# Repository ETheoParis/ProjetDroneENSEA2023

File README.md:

# ProjetDroneENSEA2023

I. Introduction :

Nous avons choisi de constituer un groupe de 5 personnes pour asservir et concevoir le PCB d'un drone. La structure en impression 3D nous a été fourni, nous nous sommes donc penchés sur la partie électronique et informatique.
Selon le dictionnaire Larousse, un drone "est un petit avion télécommandé utilisé pour des tâches diverses". Dans notre cas, le cahier des charges impose que notre drone puisse décoller, voler de manière rectiligne et atterrir après avoir volé pendant x mètres. 
Pour satisfaire le cahier des charges, nous avons divisé le travail entre les membres du groupe. Jack Du, Nesrine Mathlouthi, Cassandre Chandelier et Théo Paris se sont occupés de l’asservissement et du programme informatique pendant que Fannie Bichemin a réalisé le schématique  et l’éditeur de PCB ainsi que la soudure des composants.

I.1 Organisation :

Nous avons choisi de créer un groupe Messenger pour présenter nos avancées individuelles en dehors des séances de projet. Nous présentions nos recherches et les idées que nous avions pour résoudre les problèmes que nous avons rencontrés. De plus, nous avons réalisé dès la première séance un diagramme de Gantt pour suivre l’évolution de nos tâches respectives et du projet dans sa globalité. 

Que ce soit pour la surveillance de territoires, l'inspection de bâtiments, la cartographie de zones difficiles d'accès ou encore la livraison de colis, les drones sont devenus indispensables pour de nombreuses entreprises. Il s’agit de petits avions télécommandés utilisés pour des tâches diverses. (Larousse)

Notre objectif est d’asservir et de concevoir le PCB d’un drone quadcoptère dont la structure nous a été fournie. Nous veillerons à respecter le cahier des charges suivant : 
- Véhicule autonome
- Processeur sur carte-mère
- Pas de contrôle à distance  
- Code embarqué : C sur STM32
- Avancer, décoller
- Avancer "droit" puis de 10 m.

____________________________________________________________________________________________________________________________________________________________

I.1 Répartition des tâches :

Afin de satisfaire le cahier des charges, nous avons constitué un groupe de cinq personnes formé par :
- Fannie Bichemin (Hardware)
- Cassandre Chandelier, Jack Du, Nesrine Mathlouthi et Théo Paris (Asservissement et Software)

En ce qui concerne les livrables tels que le rapport et la soutenance, ils ont été complétés par les membres en expliquant les parties qui les concernent. 
____________________________________________________________________________________________________________________________________________________________

I.2 Organisation :

Afin de travailler facilement, nous avons choisi de créer un groupe Messenger. Ce dernier nous a permis de partager nos avancées individuelles en dehors des séances de projet. Nous présentions nos recherches et idées que nous avions pour résoudre les problèmes que nous avons rencontrés. De plus, nous avons réalisé dès la première séance un diagramme de Gantt pour suivre l’évolution de nos tâches respectives et du projet dans sa globalité. 

____________________________________________________________________________________________________________________________________________________________
____________________________________________________________________________________________________________________________________________________________

II.Hardware

II. Réalisation :

II.1 Le PCB :

Afin de réaliser le PCB, nous avons commencé par faire le schématique. 
Nous avons tout d’abord rassemblé toutes les datasheets et nous avons dessiné un diagramme pour visualiser le placement des composants (Cf figure.1 ) ainsi que le nombre de composants nécessaires pour concevoir le PCB. Par la suite, nous avons regardé les schémas présents dans les datasheets pour connaitre la valeurs des résistances et des condensateurs à placer autour du régulateur et des blocs moteurs. Nous nous sommes également aidés du TD concernant KiCad pour trouver les valeurs des résistances à placer autour de la carte STM32. 

Figure 1: Diagramme qui représente les différents éléments électroniques utilisés 

Nous avons donc abouti au schématique suivant :

	Figure 2.a : Première partie du schématique du projet

Figure 2.b : Deuxième partie du schématique du projet (les moteurs)

Le schématique comporte plusieurs parties: 

-La carte STM32
-Les boutons poussoirs
-La centrale inertielle
-La cellule de régulation
-Le connecteur SWD
-La cellule des 4 moteurs 
 
Pour ajouter les résistances, les condensateurs et les bobines, nous avons regardé les montages présentés dans les datasheets. Ces montages nous permettent de connaître le nombre et la valeur des résistances et des condensateurs à placer autour des composants centraux”.
Les problèmes rencontrés sont : 
Le choix des empreintes (faire attention au numéro à prendre le numéro 0603 et “l’option” handsolder pour faciliter la soudure ; Créer des empreintes si elles n’existent pas déjà dans les librairies en faisant surtout attention aux distances entre les pads ainsi que les contours). 
Ne pas oublier de mettre des power flag.
Les empreintes des condensateurs en fonction de leurs valeurs. 

Par la suite, nous avons placé les composants sur l’éditeur PCB. Il a fallu faire en sorte que la taille et la forme du PCB soient adaptées à l’emplacement prévu sur la base du drone imprimée en 3D. 

Figure 2.b : PCB 

Remarques:

Le PCB de gauche est la version qui aurait dû être fabriquée par le procédé “traditionnel”.  
Le PCB de droite est celui qui a été refait par Monsieur Papazouglou car il fallait modifier la manière de placer les composants puisque le PCB a été fabriqué par le système de gravure. 

Les problèmes rencontrés sont: 
Faire en sorte de relier de la manière la plus courte possible les pads entre eux. 

____________________________________________________________________________________________________________________________________________________________

Les choses à retenir:
Multiplier par 4 le “bloc moteur” (transistor, diode, connecteur, résistance, régulateur) et utiliser les coordonnées sur Kicad pour bien aligner les 4 blocs. 
Placer les condensateurs “liés” à la carte STM32 très proches du microprocesseur. 
Ne pas oublier de mettre des vias en plus un peu partout sur le PCB.

____________________________________________________________________________________________________________________________________________________________

Enfin, nous avons soudé les composants sur le PCB : 

Figure 3 : PCB soudé 

Remarque:
La dernière photo permet de montrer que les 3 diodes sont branchées dans le bon sens et qu’elles fonctionnent. 

Les problèmes rencontrés et les choses à retenir sont:
Mettre du flux pour éviter les courts circuits (surtout pour le microprocesseur et les composants très petits et très rapprochés).
Souder en premier les petits composants et en dernier les connecteurs (notamment pour éviter de les brûler).

____________________________________________________________________________________________________________________________________________________________

III. L’asservissement :

____________________________________________________________________________________________________________________________________________________________

III.1. Recherches préalables : 

Dans un premier temps, nous avons commencé par trouver une documentation adaptée à nos besoins. Il fut difficile de trouver des ressources pertinentes. Finalement, nous nous sommes basés principalement sur les articles suivants :

- Géométrie et commande des drones : https://www.techniques-ingenieur.fr/res/pdf/encyclopedia/42398210-s7818.pdf (1)
- State Space System Modelling of a Quad Copter UAV : https://arxiv.org/pdf/1908.07401.pdf (2)
- Cours d'asservissement de M.Haidar (3)

III.2. 1ère Modélisation : Discrétisation-Découplage 

L’objectif de cette modélisation est de réussir à déterminer notre commande u que nous pourrons exploiter par la suite via nos moteurs. 

Après avoir cherché la modélisation la plus proche de la réalité, on effectue une représentation d'état du système. On se base alors sur l'article (2) précédemment introduits. 

Nos paramètres d’entrées représentés par le vecteur X sont : 

l’accélération selon x 
l’accélération selon y
l’accélération selon z
l’accélération angulaire selon thêta 
l’accélération angulaire selon phi
l’accélération angulaire selon psi 

Nous avons basé notre premier modèle sur le document State Space System Modelling of a Quadcopter UAV qui donnait une représentation d'état du système.

Représentation d’état du système

Après avoir mis en forme les équations sur Matlab et défini les paramètres de l’étude, on détermine les indices relatifs en cherchant CA^rho-1 ≠ 0. 
On obtient les résultats suivants : 

On doit donc calculer les rho de chaque ligne.
Avec matlab on trouve les différent rho tel que la matrice soit inversible. Pour cela il suffit que au moins 1 des coefficient de la ligne soit non nul.
Une fois la matrice de découplage obtenu la commande est obtenu par la relation suivante.

On devrait ensuite pouvoir lier chaque commande avec la tension dans les moteurs. En effet U1 est la somme des forces, U2 le couple selon l'axe x,U3 le couple selon l'axe y,U4 le couple selon l'axe z.

On peut alors déterminer l’inverse de la matrice de découplage, on constate un problème car le système possède 4 commandes pour 6 sorties. On ne peut donc pas découpler les variables du système car le système est sous-actionné (cf cours d'asservissement).

Nous avons donc changé de modèle pour se baser sur celui de la simulation quadcopter (par Monsieur Djemai).

III. 3 Nouvelle modélisation :

On se base sur une nouvelle modélisation qui nous donne directement l'équation des couples et de la somme des forces des moteurs en fonction des accélérations. 
Il faudrait trouver un moyen de déterminer les fonctions seuil et les constants réstantes. On sait déja que mu est la force minimum des moteurs pour faire décoler de drone. Avec plus de temps il aurait surment été possible de faire fonctionner l'asservissement.

____________________________________________________________________________________________________________________________________________________________
____________________________________________________________________________________________________________________________________________________________

IV. Software :

##
Pour la partie code en C, le code sur carte NUCLEOH7A3ZI est présent sur le projet NUCLEOH7A3ZI_MPU6050. Nous n'avons pas optimisé et clarifié totalement le code suite à un problème de makefile sur les fonctions crées automatiquement par STM32 via l'ioc.
Le code a été également porté sur un autre projet (DroneFlying en l'occurence) pour le code à implémenter sur le PCB du drone.

1. PWM

En ce qui concerne le contrôle des 4 moteurs, on a décidé qu'elle se ferrait via une PWM (Pulse Width Modulation ou Modulation de largeur d'impulsion en français). 
La méthode PWM consiste à faire varier le rapport cyclique à une fréquence fixe pour ajuster la tension à la valeur cible souhaitée.

![image] 
(https://github.com/ETheoParis/ProjetDroneENSEA2023/blob/main/Images/PWM.png)

Figure 4 : PWM Fonctionnement

![image] 
(https://github.com/ETheoParis/ProjetDroneENSEA2023/blob/main/Images/PWM_Diagramme.png)

Figure 5 : Diagramme PWM 

La fréquence fixe avec laquelle nous travaillons est alors de 20kHz afin d'éviter les fréquences audibles par l'Homme.
Dans le cas de notre test sur NUCLEO, nous avons configuré un timer via l'interface ioc sur STL32CubeIDE. La fréquence d'horloge de base de la carte était de 80MHz. 
Nous avons alors ajouté un PSC (prescaler) "4-1" et un rapport de division ARR (auto reload register) de "1000-1" afin d'obtenir une fréquence d'horloge d'étude de 20kHz.

![image]
(https://github.com/ETheoParis/ProjetDroneENSEA2023/blob/main/Images/PWM_Config1.png)

![image]
(https://github.com/ETheoParis/ProjetDroneENSEA2023/blob/main/Images/PWM_Config.png)

Figure 6 & 7 : Configuration Timer pour PWM 

D'ailleurs, en ce qui concerne STM32CubeIDE, il faut penser à générer automatiquement les fichiers de code .c et .h implémentés par STM lors de l'utilisation d'un port GPIO quelconque ou bien d'un timer comme c'est le cas actuellement.
(XXX.ioc -> Project Manager -> Code Generator -> Generate peripheral initialization as a pair of '.c/.h' files per peripheral)

En ce qui concerne le fonctionnement, on doit alors déterminer une valeur de comparaison CCR afin d'avoir le rapport cyclique souhaitée. 
Dans le cas de notre code, nous avons testé avec sortie sur l'oscilloscope la PWM pour différentes valeurs de CCR choisie (200, 400, 800).

![image]
(https://github.com/ETheoParis/ProjetDroneENSEA2023/blob/main/Images/PWM_Oscilloscope.png)

Figure 8 : Test PWM sur oscilloscope

La fonction calculCCR permet de faire le lien entre une tension voulue et la PWM. Son résultat serait utilisé dans la fonction __HAL_TIM_SET_COMPARE pour changer la valeurs de la PWM.
La fonction CalculCCR n'a pas pu être vérifiée et optimisée avec les caractéristiques des moteurs (notamment la constance de couple Kc propres à nos moteurs) dans le cas de notre drone puisqu'on a eu un problème hardware sur le PCB qui a empêché les tests. Toutefois, la PWM était effectivement fonctionnel avec affichage sur l'oscilloscope. Nous aurions encore eu à optmiser le choix de CCR afin d'être bien compris dans la plage de fonctionnement des moteurs (en terme de tensions/vitesse de rotation acceptées). Cela aurait pu se faire en adoptant un ordre croissant de CCR afin d'éviter d'endommager les moteurs.

2. MPU6050

Pour contrôler la trajectoire du drone et le stabiliser, nous avons besoin d'un gyroscope et d'un accéléromètre qui permet d'obtenir des valeurs de positions et d'angle après traitement. On a donc utilisé une centrale inertielle qui comprend les deux : le MPU6050.
Cette centrale inertielle communique en bus I2C avec le microprocesseur et transmet les données via UART. On définit les ports de transmissions directement sur l'ioc, comme avec la PWM. On a donc également pu se reposer sur les bibliothèques HAL et UART déjà intégrée et propres à STM32.

Pour la récupération des données de la centrale inertielle on utilise HAL_TIM_PeriodElapsedCallback pour échantillonner la récupération des données à la fréquence du timer. Les données sont lues par HAL_I2C_Mem_Read puis enregistrées dans Rec_Data et recopier dans x, y, z. HAL_UART_Transmit permet de tester le fonctionnement du MPU en récupérant les données via une interface d'affichage tel que Putty sur Windows.

![image]
(https://github.com/ETheoParis/ProjetDroneENSEA2023/blob/main/Images/Putty.png)

Figure 9 : Affichage des valeurs d'accélération et de vitesse angulaire obtenues de la centrale inertielle sur Putty.

Toutefois, en ce qui concerne les valeurs, on observe une variation en l'absence même de mouvement. Cela est problématique par rapport au fait que l'on intègre 2 fois pour obtenir la position, on aurait dans ce cas beaucoup trop d'incertitudes et de variations par rapport à la réalité au fur et à mesure que le drone vole et se déplace. 
Il faut donc travailler sur l'échelle de précision du capteur mais nous n'avons pas pu améliorer ce point-ci par manque de temps. Nous aurions également pu filtrer les valeurs et ne garder que celles qui étaient pertinentes.

3. Fonctions intermédiaires

Nous avons également crée des fonctions intermédiaires qu'on aurait été appelé à utiliser dans le cas du déplacement de drone, toutefois, comme nous étions assez occupé par l'asservissement et l'optimisation des autres parties, nous n'avons pas pu aboutir à un stade où nous utilisions ces fonctions.

int calculVitesse1D(int acceleration, int vitesseActuelle, int pas);
void primitive(VECTEUR* derivee, VECTEUR* constante,VECTEUR* primitive, int pas);
void calculVitesse(VECTEUR* acceleration,VECTEUR* vitesseActuelle,VECTEUR* nouvelleVitesse, int pas);
void calculPosition(VECTEUR* vitesse,VECTEUR* positionActuelle,VECTEUR* nouvellePosition,int pas);
int calculCourantMoteur(int reg);
void recopie(VECTEUR * nouveau, VECTEUR * ancien);

4. Optimisation

Pour éviter que le drone ne se pose trop violemment/rapidement, ce qui aurait endommagé les composants, nous aurions pu mesurer et vérifier la variation de résistance vis-à-vis de la rotation des hélices de chaque moteur. Une résistance plus faible aurait témoigné du fait qu'il y a une réaction normale de pousée vis-à-vis du sol et donc cela aurait signifié une proximité plus importante avec le sol.

La fonction calculCourantMoteur utilise la tension au borne de la résistance Rshunt pour calculer le courant dans le moteur. Son résultat devait servir à mesurer la distance avec le sol. Bien que nous avons bien ajouté une résistance pour cette optimisation, nous n'avons malheureusement pas pu l'implémenter et la tester en plus du cahier des charges initial par manque de temps et contraintes techniques.

_______________________________________________________________________

En terme d'optimisation, on aurait également pu améliorer le code et diminuer son empreinte en terme de ressources inutiles, notamment dans le call de fonctions bien qu'on travaille déjà en C, langage avec une empreinte assez faible.
Le code aurait également pu être amélioré dans son agencement si nous avions réglé le problème d'un MakeFile affecté.

_______________________________________________________________________
_____________________________________________________________________________________

QUESTIONS OBJECTIFS DEVELOPPEMENT DURABLE:
_____________________________________________________________________________________________________________________________________
=> Quelle réflexion avez-vous mené au cours de ce projet autour de la limitation de la consommation d'énergie ?

Notre drone a été modélisé tout en prenant en compte la limitation de la consommation d'énergie. Les critères pris en compte sont :

- Le choix des composants (développé dans la question suivante) qui doit favoriser l'économie d'énergie. (batterie avec bonne capacité et poids raisonnable)

- La conception du drone (favorisation des matériaux légers pour la structure=> réduction du poids total=> travail plus efficace du moteur et aérodynamique du drone étudiée et donc une autonomie accrûe -> Apporte de nouvelles fonctionnalités qui n'étaient pas possibles)

- Usage de technologies avancées (centrale inertielle qui regroupe à la fois un accéléromètre mais aussi un gyroscope. Nous avons donc l'échange de toutes les données externes via seulement une interface I2C et évite de multiplier le nombre de composants sur le PCB qui alourdi le drone et donc augmente la consommation d'énergie et code avec un langage de bas niveau, C, donc à plutôt faible empreinte carbone).

_____________________________________________________________________________________________________________________________________
=>Expliquer les critères de choix des composants de votre projet (critères environnementaux, de disponibilité, d'emprise spatiale, autres).

Le choix des composants est primordial lors de la réalisation d'un projet. Il existe plusieurs critères à prendre en considération:

-Critères environnementaux : Il faut effectivement privilégier le fait d'utiliser le moins de composants possibles sur notre PCB et sinon utiliser ceux qui présente une efficience importante en terme de consommation.

-Critères de disponibilité : Il est nécessaire de privilégier les composants des fournisseurs les plus fiables (Farnell/RS/Mouser/Digikey/Gotronic...). Chez ces derniers, le choix de matériel est largement plus important et des datasheets des composants y sont proposées.

-Critères d'emprise spatiale : (taille et poids : les composants trop lourds peuvent avoir un impact négatif sur les caractéristiques de vol du drone)

On peut également prendre en compte les critères suivants : le coût/les performances et la compatibilité avec d'autres composants du système. 

Concentrons-nous désormais sur chaque composant : 
- Batterie : Nous avons choisi une batterie de capacité 3,7 Wh avec une masse = 30g afin de respecter les critères d'emprise spatiale.La capacité a été choisie afin de permettre le respect du cahier des charges (vol sur 10m avec montée et descente) sans trop impacter l'autonomie (puisque la charge influe sur la vitesse de rotation des hélices pour maintenir le drone en vol).

- Régulateur de tension (17395xx36): Notre choix de composant présente une efficité maximale de 97%. Cela est bien plus pertinent dans le cas d'un drone avec un accumulateur de faible capacité qu'un régulateur linéaire/LDO qui présente une efficacité maximale moindre.

D'ailleurs, la différence d'efficacité entre un régulateur linéaire et un régulateur à découpage s'explique par leur fonctionnement différent :
Les régulateurs linéaires, tels que les régulateurs de type LDO (Low Drop-Out), fonctionnent en utilisant une configuration de transistors pour réguler la tension de sortie. Ils offrent une sortie stable et régulée, mais la différence de tension entre l'entrée et la sortie (la "chute de tension" ou "drop-out") entraîne une dissipation de puissance importante sous forme de chaleur.  (R*I^2) Cela signifie que les régulateurs linéaires ont une efficacité relativement faible, surtout lorsque la différence de tension entre l'entrée et la sortie est élevée. 

En revanche, les régulateurs à découpage fonctionnent en commutant rapidement entre un état actif et un état inactif pour maintenir une tension de sortie régulée. Ils utilisent des inductances et des condensateurs pour stocker et transférer l'énergie de manière efficace. Les régulateurs à découpage sont capables de convertir l'énergie de manière beaucoup plus efficace que les régulateurs linéaires, car ils minimisent les pertes de puissance sous forme de chaleur. Cela se traduit par une meilleure efficacité énergétique et une dissipation de chaleur réduite.

- Moteur: Les critères pris en compte sont principalement la consommation, la taille, la puissance délivrée, le poids et la vitesse (rpm(tr/min) = constante de vélocité * tension. Le rpm va influencer sur la stabilité du vol. Plus celui-ci est faible, plus le vol sera stable). Notre choix s'est porté sur Moteurs Brossés Axe 1.0mm pour Quadricoptère Tiny 8X RC.

- Hélices: Nous prenons en considération leurs longueurs, leurs pas ainsi que leurs compositions (matériaux).

- Châssis: Nous utilisons un châssis qui est fait en PLA, l'acide polylactique qui est en plastique biodégradable (sous certaines conditions) et recyclable par extrudeuse (le plus simple et moins couteux) ou bien par dépolymérisation et repolymérisation. Il s'agit d'un matériau à faible empreinte carbone, notamment dans le cas d'un prototypage comme on est ammené à faire, il s'agit d'une bonne solution logistique et environnemental. 
_____________________________________________________________________________________________________________________________________
=> Sources :

-Datasheets des composants 
-https://www.pilgrim-technology.com/drones-et-environnement/

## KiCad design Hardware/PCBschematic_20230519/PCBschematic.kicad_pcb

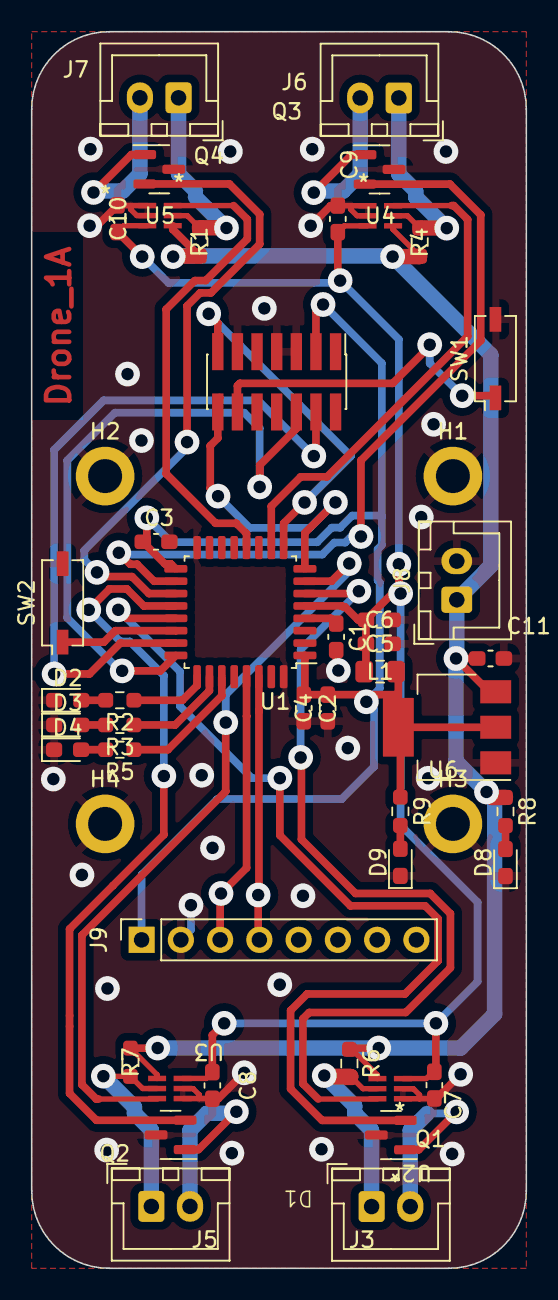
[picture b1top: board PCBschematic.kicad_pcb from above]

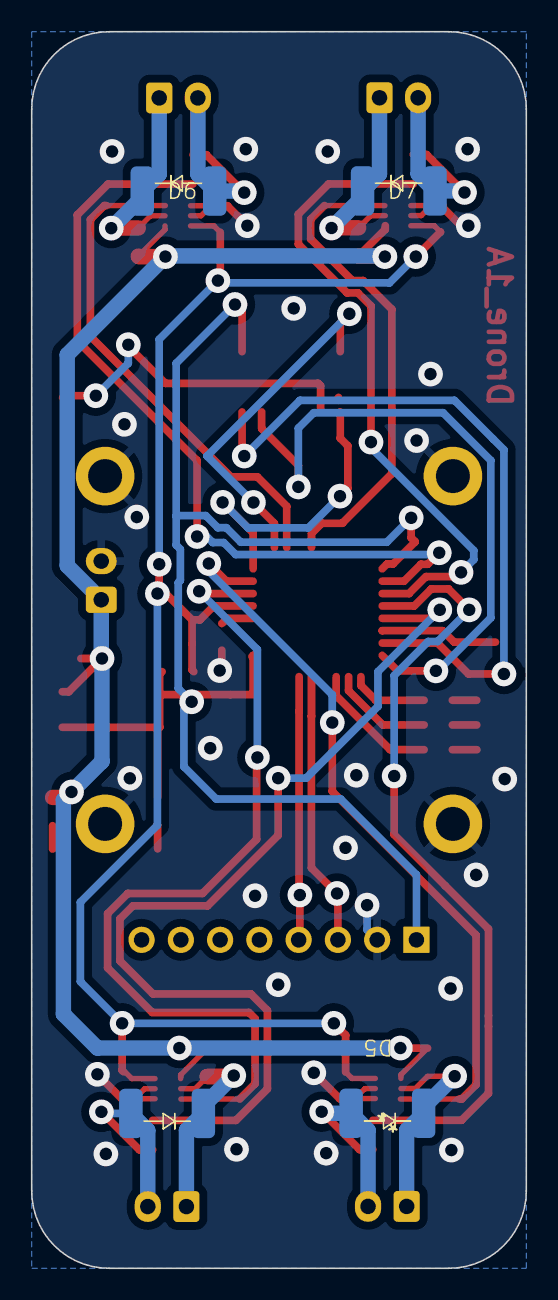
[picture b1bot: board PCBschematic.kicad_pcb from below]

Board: 2 copper layers, 32.0 x 80.0 mm, 53 parts (4 on the bottom side), 36 nets.

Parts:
C1: 100nF; C_0603_1608Metric_Pad1.08x0.95mm_HandSolder
C2: 4.7uF; C_0603_1608Metric_Pad1.08x0.95mm_HandSolder
C3, C4: 100n; C_0603_1608Metric_Pad1.08x0.95mm_HandSolder
C5: 1u; C_0603_1608Metric_Pad1.08x0.95mm_HandSolder
C6: 10n; C_0603_1608Metric_Pad1.08x0.95mm_HandSolder
C7, C8, C9, C10: 0.1u; C_0603_1608Metric_Pad1.08x0.95mm_HandSolder
C11: 10uF; C_0603_1608Metric_Pad1.08x0.95mm_HandSolder
D1, D5, D6, D7: VS-30BQ0115HM3; DiodeVS-30BQ015HM3
D2, D3, D4, D8, D9: LED; LED_0603_1608Metric_Pad1.05x0.95mm_HandSolder
H1, H2, H3, H4: MountingHole_Pad; MountingHole_2.2mm_M2_DIN965_Pad
J3, J5, J6, J7: Conn_01x02; JST_XH_B2B-XH-A_1x02_P2.50mm_Vertical
J4: Conn_02x07_Odd_Even; PinHeader_2x07_P1.27mm_Vertical_SMD
J8: batterie; JST_XH_B2B-XH-A_1x02_P2.50mm_Vertical
J9: Conn_01x08; PinSocket_1x08_P2.54mm_Vertical
L1: 39n; L_0805_2012Metric_Pad1.15x1.40mm_HandSolder
Q1, Q2, Q3, Q4: SQ2310ES; SOT-23
R1, R4, R6, R7: R_Small; R_0603_1608Metric_Pad0.98x0.95mm_HandSolder
R2, R3, R5, R8, R9: 1k; R_0603_1608Metric_Pad0.98x0.95mm_HandSolder
SW1, SW2: SW_Push; SW_DIP_SPSTx01_Slide_Copal_CHS-01A_W5.08mm_P1.27mm_JPin
U1: STM32L412KBTx; LQFP-32_7x7mm_P0.8mm
U2, U3, U4, U5: NCS210; SC70-6_ONS
U6: regulator_17395xx36; SOT-223-3_TabPin2

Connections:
+3.3V: C2.1, C3.1, C4.1, J4.3, J9.1, L1.1, R9.1, U1.1 (VDD), U1.17 (VDD), U6.2 (VO)
+3.3VA: C5.1, C6.1, C7.2, C8.2, C9.2, C10.2, L1.2, U1.5 (VDDA), U2.3 (Vs), U3.3 (Vs), U4.3 (Vs), U5.3 (Vs)
AO1: U1.6 (PA0), U2.6 (OUT)
AO2: U1.7 (PA1), U3.6 (OUT)
AO3: U1.10 (PA4), U4.6 (OUT)
AO4: U1.12 (PA6), U5.6 (OUT)
GND: C1.2, C2.2, C3.2, C4.2, C5.2, C6.2, C7.1, C8.1, C9.1, C10.1, C11.2, D2.1 (K), D3.1 (K), D4.1 (K), D8.1 (K), D9.1 (K), H1.1, H2.1, H3.1, H4.1, J4.5, J4.7, J4.11, J8.2, J9.2, Q1.3 (S), Q2.3 (S), Q3.3 (S), Q4.3 (S), SW1.2, SW2.2, U1.16 (VSS), U1.32 (VSS), U2.1 (REF), U2.2 (GND), U3.1 (REF), U3.2 (GND), U4.1 (REF), U4.2 (GND), U5.1 (REF), U5.2 (GND), U6.1 (GND)
I2C_SCL: J9.3, U1.29 (PB6)
I2C_SDA: J9.4, U1.30 (PB7)
LED_STATUS: R5.1, U1.27 (PB4)
LED_STOP: R3.1, U1.26 (PB3)
LED_Start: R2.1, U1.25 (PA15)
unnamed: D1.2 (A), J3.2, Q1.1 (D)
unnamed: D1.1 (K), J3.1, R6.2, U2.5 (-IN)
unnamed: D2.2 (A), R2.2
unnamed: D3.2 (A), R3.2
unnamed: D4.2 (A), R5.2
unnamed: D5.2 (A), J5.2, Q2.1 (D)
unnamed: D5.1 (K), J5.1, R7.2, U3.5 (-IN)
unnamed: D6.2 (A), J6.2, Q3.1 (D)
unnamed: D6.1 (K), J6.1, R4.2, U4.5 (-IN)
unnamed: D7.2 (A), J7.2, Q4.1 (D)
unnamed: D7.1 (K), J7.1, R1.2, U5.5 (-IN)
unnamed: D8.2 (A), R8.2
unnamed: D9.2 (A), R9.2
PWM_1: Q1.2 (G), U1.21 (PA11)
PWM_2: Q2.2 (G), U1.20 (PA10)
PWM_3: Q3.2 (G), U1.18 (PA8)
PWM_4: Q4.2 (G), U1.19 (PA9)
Reset_Buton: C1.1, J4.12, SW1.1, U1.4 (NRST)
SWDCK: J4.6, U1.24 (PA14)
SWDIO: J4.4, U1.23 (PA13)
Start_Buton: SW2.1, U1.22 (PA12)
USART2_RX: J4.13, U1.9 (PA3)
USART2_TX: J4.14, U1.8 (PA2)
VCC: C11.1, J8.1, R1.1, R4.1, R6.1, R7.1, R8.1, U2.4 (+IN), U3.4 (+IN), U4.4 (+IN), U5.4 (+IN), U6.3 (VI)

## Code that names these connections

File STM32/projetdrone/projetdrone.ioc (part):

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Mcu.Name=STM32L412KBTx
Mcu.Package=LQFP32
Mcu.Name=STM32L412KBTx
Mcu.Package=LQFP32
Mcu.UserName=STM32L412KBTx
PA0-CK_IN.GPIOParameters=GPIO_Label
PA0-CK_IN.GPIO_Label=A01
PA0-CK_IN.Signal=ADCx_IN5
PA1.GPIOParameters=GPIO_Label
PA1.GPIO_Label=A02
PA1.Signal=ADCx_IN6
PA10.GPIOParameters=GPIO_Label
PA10.GPIO_Label=PWM_3
PA10.Signal=S_TIM1_CH3
PA11.GPIOParameters=GPIO_Label
PA11.GPIO_Label=PWM_4
PA11.Signal=S_TIM1_CH4
PA15\ (JTDI).GPIOParameters=GPIO_Label
PA15\ (JTDI).GPIO_Label=LED_START
PA13\ (JTMS/SWDIO).Mode=Serial_Wire
PA13\ (JTMS/SWDIO).Signal=SYS_JTMS-SWDIO
PA14\ (JTCK/SWCLK).Mode=Serial_Wire
PA14\ (JTCK/SWCLK).Signal=SYS_JTCK-SWCLK
PA15\ (JTDI).GPIOParameters=GPIO_Label
PA15\ (JTDI).GPIO_Label=LED_Start
PA15\ (JTDI).Signal=GPIO_Output
PA2.Mode=Asynchronous
PA2.Signal=USART2_TX
PA3.Mode=Asynchronous
PA3.Signal=USART2_RX
PA4.GPIOParameters=GPIO_Label
PA4.GPIO_Label=A03
PA4.Signal=ADCx_IN9
PA6.GPIOParameters=GPIO_Label
PA6.GPIO_Label=A04
PA6.Signal=ADCx_IN11
PA7.Signal=QUADSPI_BK1_IO2
PA8.GPIOParameters=GPIO_Label
PA8.GPIO_Label=PWM_1
PA3.Mode=Asynchronous
PA3.Signal=USART2_RX
PA6.Signal=ADCx_IN11
PA7.Signal=ADCx_IN12
PA8.Signal=S_TIM1_CH1
PA9.GPIOParameters=GPIO_Label
PA9.GPIO_Label=PWM_2
PA9.Signal=S_TIM1_CH2
PB0.Signal=ADCx_IN15
PB1.Signal=ADCx_IN16
PB3\ (JTDO/TRACESWO).GPIOParameters=GPIO_Label
PB3\ (JTDO/TRACESWO).GPIO_Label=LED_stop
PB3\ (JTDO/TRACESWO).Signal=GPIO_Output
PB4\ (NJTRST).GPIOParameters=GPIO_Label
PB4\ (NJTRST).GPIO_Label=LED_status
PB4\ (NJTRST).GPIO_Label=LED_Status
PB4\ (NJTRST).Signal=GPIO_Output
PB6.Mode=I2C
PB6.Signal=I2C1_SCL
PB7.Mode=I2C
PB7.Signal=I2C1_SDA
PC15-OSC32_OUT\ (PC15).GPIOParameters=GPIO_Label
PC15-OSC32_OUT\ (PC15).GPIO_Label=BTN_Start
PC15-OSC32_OUT\ (PC15).Signal=GPXTI15
RCC.HSE_VALUE=8000000
RCC.SYSCLKFreq_VALUE=80000000
RCC.SYSCLKSource=RCC_SYSCLKSOURCE_PLLCLK
board=custom

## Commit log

2023-04-03 Add files via upload
    A ranger dans Data sheets.
2023-04-03 Ajout du diagramme PCB
2023-04-07 test Giannini
2023-04-07 del test
2023-04-07 add folders
2023-04-07 add datasheets
2023-04-08 Diagramme fonctions.drawio
2023-04-08 Diagramme fonctions.pdf
2023-04-09 Mettre à jour Diagramme sans nom.drawio
2023-04-09 Ajouté(e) Diagramme sans nom.drawio.pdf
2023-04-09 diagramme1
2023-04-09 impact_construction
2023-04-11 revue 11 avril
2023-04-11 del fichier.txt
2023-04-11 Ajouté(e) fonction Drone.drawio
2023-04-11 Mettre à jour fonction Drone.drawio
2023-04-11 Update DataSheets
2023-04-11 Ajouté(e) PWM
2023-04-11 Update DataSheets..
2023-04-11 Mettre à jour PWM
2023-04-11 debutschematicpcb
2023-04-11 debutschematicpcbetstm32
2023-04-11 debutschematicpcbetstm32v0
2023-04-11 schematicavancee
2023-04-14 newversion
2023-04-15 update ioc
2023-04-15 stm32_pin_parametre
2023-04-15 pcb schematic sans erreur et editeur sans erreur egalement
2023-04-15 fichier_aide_asservissement
2023-04-15 ajout des GND sur le pcb
2023-04-17 correction
2023-04-17 Update doc annexe
2023-04-17 Création dossier asservissement
2023-04-17 pcb en cours de correction
2023-04-17 Ajout jpg Gantt
2023-04-22 avancementpcb
2023-04-22 pcb_mise_en_place_okay_reste_3_erreurs git commit -m pcb_mise_en_place_okay_reste_3_erreurs
2023-04-25 modif pcb
2023-05-02 routage v1
2023-05-09 Ajouté(e) Diagramme explication asservissement.drawio
2023-05-09 pcbpluspetot
2023-05-09 pcb_tailledrone
2023-05-09 Update PCB Schem + Objectif dev durable
2023-05-09 Upload MATLAB file
2023-05-13 nouveau pcb
2023-05-15 Update asservissement folder
2023-05-15 routage v2
2023-05-15 v2_nom
2023-05-16 Update PWM
2023-05-16 routage_V2_fini
2023-05-19 add pcb with bigger vias
2023-05-22 Update Questions
2023-05-22 Update asserv Matlab
2023-05-22 début_CR
2023-05-23 Finalisation questions
2023-05-23 Ajout livre
2023-05-23 code MPU
2023-05-23 add mpu6050 accelero mesurement
2023-05-25 code MPU GYRO
2023-05-26 Update MPU6050 and PWM
2023-05-30 PWM works now
2023-05-30 Modif readme
2023-05-30 Update Software
2023-06-01 Ajouté(e) fonctions PWM.drawio
2023-06-01 Mettre à jour fonctions PWM.drawio
2023-06-01 Ajouté(e) Fonctions MPU5060.drawio
2023-06-01 Mettre à jour Fonctions MPU5060.drawio
2023-06-02 Update software and adding STM32 project
2023-06-02 ajout fonction C
2023-06-02 Ajout de texte au CR
2023-06-02 reorganisation des fichiers et des dossiers
2023-06-02 ajout photos CR
2023-06-02 essai photo
2023-06-02 ajout photos
2023-06-02 ajout des URLS des photos pour le Cr
2023-06-02 fin ajout images partie PCB
2023-06-04 ajout description composants sur schématique
2023-06-06 organisation fonction C
2023-06-06 Update small details
2023-06-09 udate asservissement readme.md
2023-06-09 Added comments in the code
2023-06-09 Update README and solved displaying issues
2023-06-09 merged the 2 README
2023-06-09 Merged the 2 README and reorganized it
2023-06-09 Updated folders and added durable development to README
2023-06-09 Update README : added software and asserv and Update Images for README
2023-06-09 Update layout on README and Images
2023-06-09 update images
2023-06-09 small changes
2023-06-09 Update small changes
2023-06-09 Update last changes
2023-06-09 Update for LDO/Découpage regulator differences
2023-06-09 update last few changes
